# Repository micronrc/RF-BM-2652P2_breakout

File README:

A simple breakout board for the RF-Star RF-BM-2652P2 module
 which is based on the TI CC2652P, a 20dBm capable 2.4GHz SoC.
 
 For info on the CC2652P, see https://www.ti.com/product/CC2652P

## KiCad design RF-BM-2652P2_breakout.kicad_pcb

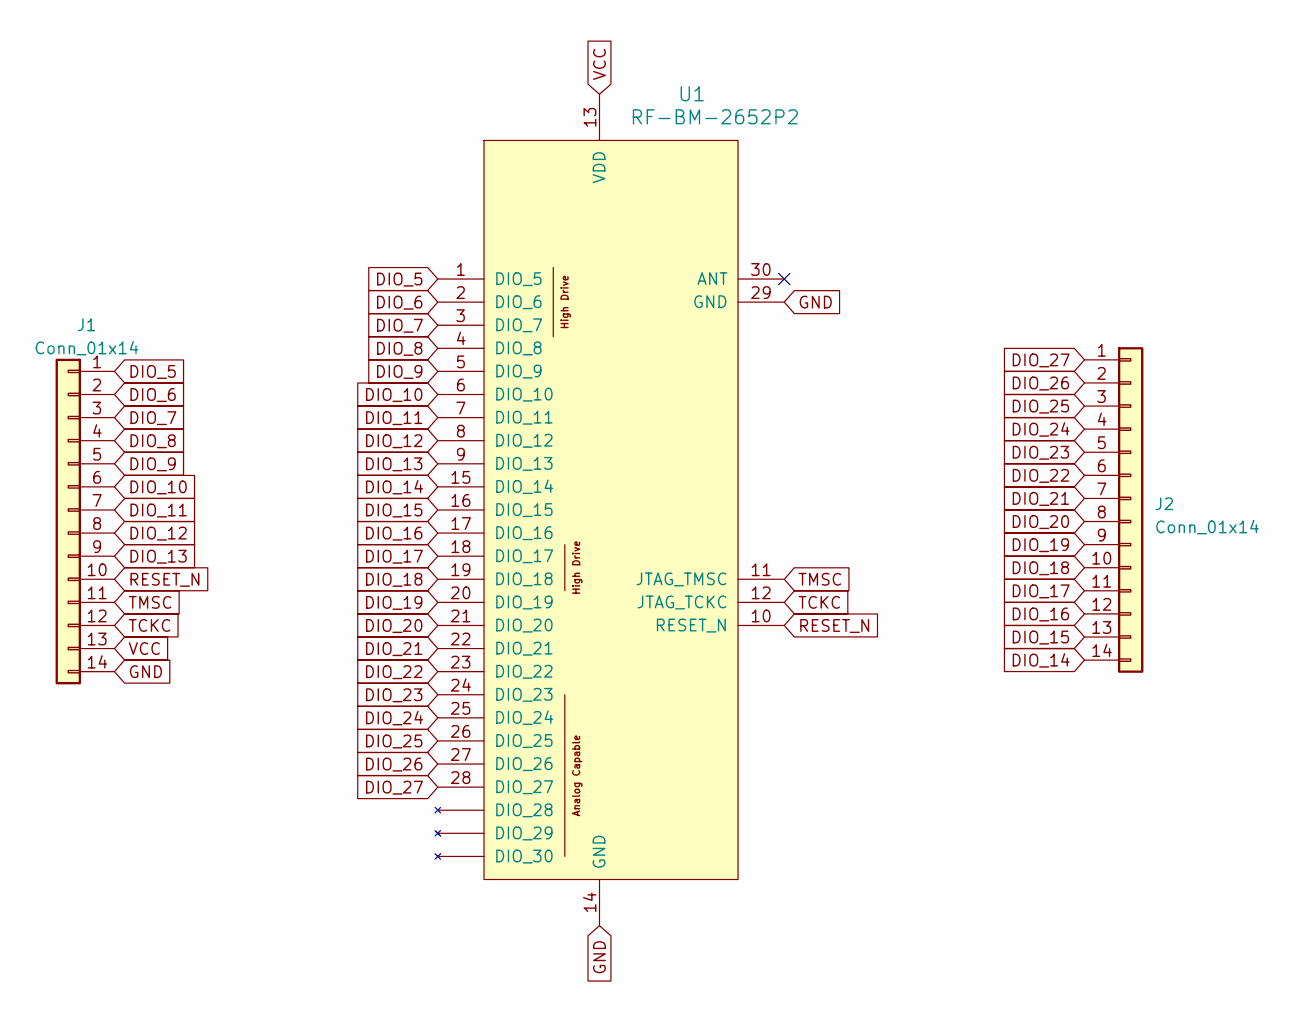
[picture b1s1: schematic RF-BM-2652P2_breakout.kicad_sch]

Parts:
J1, J2: Conn_01x14; PinHeader_1x14_P2.54mm_Vertical
U1: RF-BM-2652P2; MPN RF-BM-2652P2

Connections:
DIO_5: J1.1, U1.1 (DIO_5)
DIO_6: J1.2, U1.2 (DIO_6)
DIO_7: J1.3, U1.3 (DIO_7)
DIO_8: J1.4, U1.4 (DIO_8)
DIO_9: J1.5, U1.5 (DIO_9)
DIO_10: J1.6, U1.6 (DIO_10)
DIO_11: J1.7, U1.7 (DIO_11)
DIO_12: J1.8, U1.8 (DIO_12)
DIO_13: J1.9, U1.9 (DIO_13)
DIO_14: J2.14, U1.15 (DIO_14)
DIO_15: J2.13, U1.16 (DIO_15)
DIO_16: J2.12, U1.17 (DIO_16)
DIO_17: J2.11, U1.18 (DIO_17)
DIO_18: J2.10, U1.19 (DIO_18)
DIO_19: J2.9, U1.20 (DIO_19)
DIO_20: J2.8, U1.21 (DIO_20)
DIO_21: J2.7, U1.22 (DIO_21)
DIO_22: J2.6, U1.23 (DIO_22)
DIO_23: J2.5, U1.24 (DIO_23)
DIO_24: J2.4, U1.25 (DIO_24)
DIO_25: J2.3, U1.26 (DIO_25)
DIO_26: J2.2, U1.27 (DIO_26)
DIO_27: J2.1, U1.28 (DIO_27)
GND: J1.14, U1.14 (GND), U1.29 (GND)
RESET_N: J1.10, U1.10 (RESET_N)
TCKC: J1.12, U1.12 (JTAG_TCKC)
TMSC: J1.11, U1.11 (JTAG_TMSC)
VCC: J1.13, U1.13 (VDD)

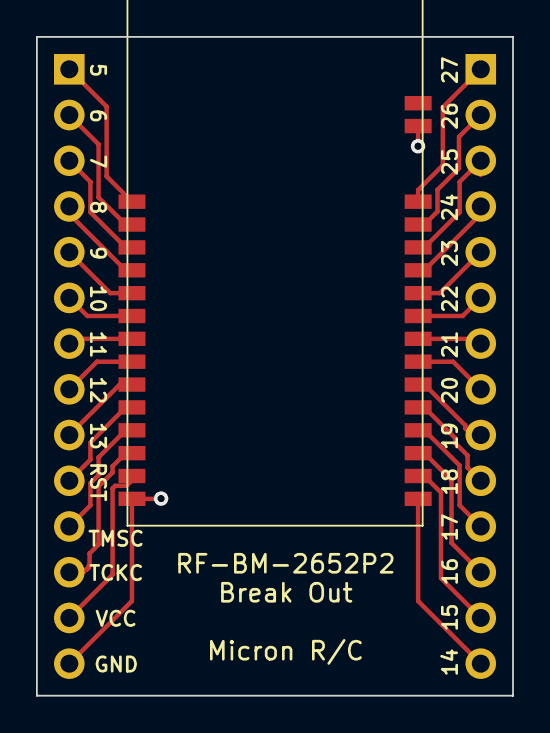
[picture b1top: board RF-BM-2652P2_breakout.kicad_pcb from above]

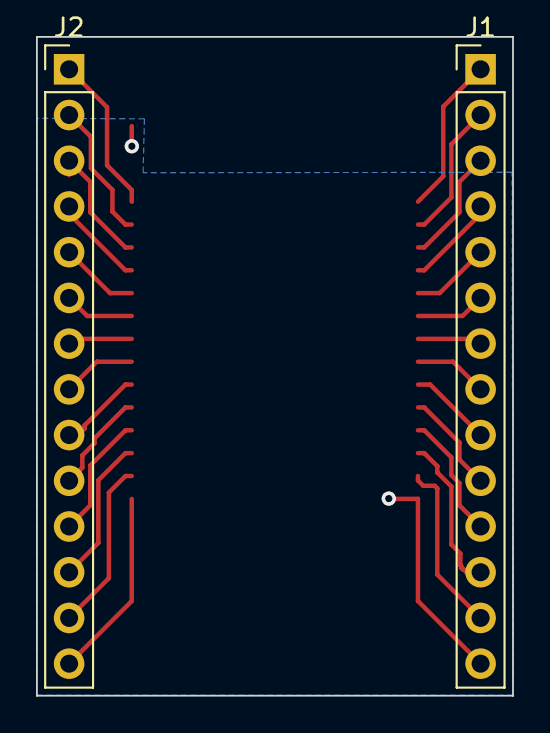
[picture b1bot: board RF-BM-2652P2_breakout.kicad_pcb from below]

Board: 2 copper layers, 26.4 x 36.6 mm, 3 parts (2 on the bottom side), 28 nets.
